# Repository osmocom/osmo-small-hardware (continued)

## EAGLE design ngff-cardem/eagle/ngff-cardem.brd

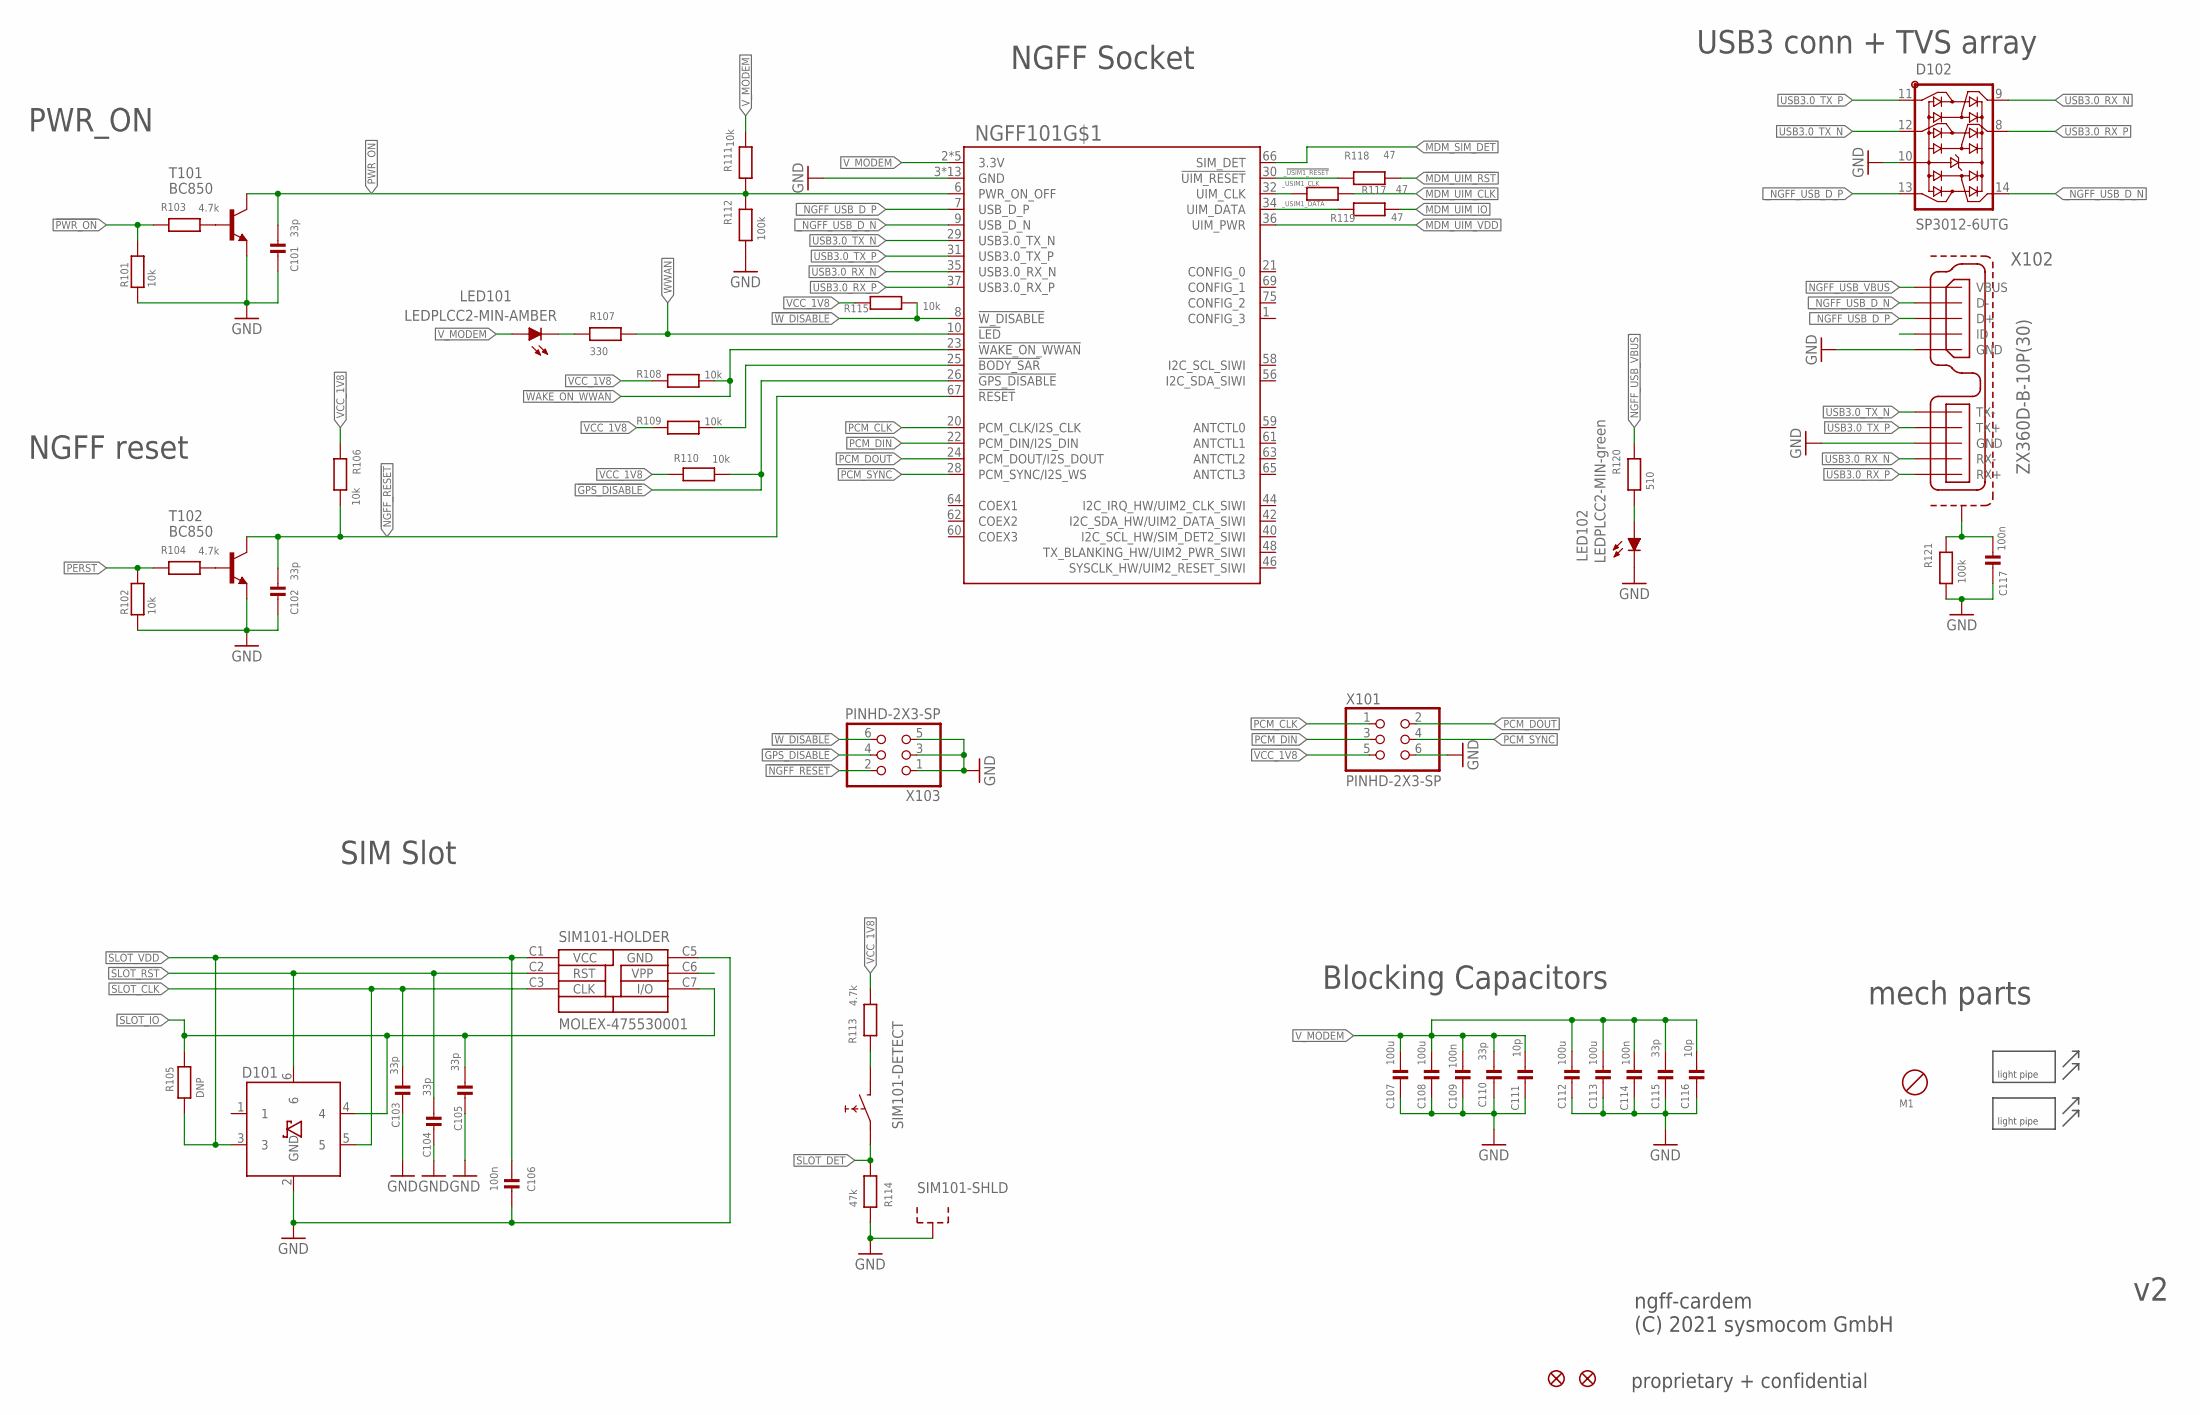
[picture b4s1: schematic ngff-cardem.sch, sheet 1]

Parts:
C101, C102, C103, C104, C105, C110, C115: 33p; _0402; MANUFACTURERPARTNUMBER CL05C330JB5NNNC
C106, C109, C114, C117: 100n; _0603; MANUFACTURERPARTNUMBER CC0603KRX7R7BB104
C107, C108, C112, C113: 100u; 1206; MANUFACTURERPARTNUMBER C3216X5R0J107M160AB
C111, C116: 10p; _0603; MANUFACTURERPARTNUMBER C0603C100F5GAC7867
D101: PESD5V0UBV; SOT666; MANUFACTURERPARTNUMBER PESD5V0U5BV,115
D102: SP3012-6UTG; UDFN-14; MANUFACTURERPARTNUMBER SP3012-06UTG
JP102, JP103: FIDUCIALUFIDUCIAL; MICRO-FIDUCIAL; MANUFACTURERPARTNUMBER UNKNOWN MANUFACTURER PART NUMBER
LED101: LEDPLCC2-MIN-AMBER; PLCC2-MIN; MANUFACTURERPARTNUMBER LO T676-S1T1-24-Z
LED102: LEDPLCC2-MIN-green; PLCC2-MIN; MANUFACTURERPARTNUMBER HSME-A100-M02J1
M2, M3: MENTOR_12701001; 1270.1001; MANUFACTURERPARTNUMBER UNKNOWN MANUFACTURER PART NUMBER
NGFF101: NGFF_B-NSOL; NGFF_3042_3052_NSOL; MANUFACTURERPARTNUMBER 2199230-3
R101, R102, R106, R108, R109, R110, R111, R115: 10k; _0603; MANUFACTURERPARTNUMBER CRG0603F10K/10
R103, R104, R113: 4.7k; _0603; MANUFACTURERPARTNUMBER RC0603JR-074K7L
R105: DNP; _0603; MANUFACTURERPARTNUMBER CRG0603F10K/10
R107: 330; _0603; MANUFACTURERPARTNUMBER RC0603FR-07330RL
R112, R121: 100k; _0603; MANUFACTURERPARTNUMBER RMCF0603FT100K
R114: 47k; _0603; MANUFACTURERPARTNUMBER RMCF0603FT47K0
R117, R118, R119: 47; _0402; MANUFACTURERPARTNUMBER CRGCQ0402F47R
R120: 510; _0603; MANUFACTURERPARTNUMBER RMCF0603FT510R
SIM101: MOLEX-475530001; MANUFACTURERPARTNUMBER 0475530001
T101, T102: BC850; SOT23-BEC; MANUFACTURERPARTNUMBER BC850C,235
X101, X103: PINHD-2X3-SP; 2X03; MANUFACTURERPARTNUMBER PR20203VBDN
X102: ZX360D-B-10P(30); ZX360D-B; MANUFACTURERPARTNUMBER ZX360D-B-10P(30)

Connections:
!BODY_SAR: NGFF101.25 (!BODY_SAR), R109.1
!GPS_DISABLE: NGFF101.26 (!GPS_DISABLE), R110.1, X103.4
!MDM_UIM_RST: R118.2; also elsewhere on the board
!NGFF_RESET: C102.1, NGFF101.67 (!RESET), R106.1, T102.C, X103.2
!PWR_ON: R101.1, R103.2; also elsewhere on the board
!SLOT_RST: C104.1, D101.6, SIM101.C2 (RST); also elsewhere on the board
!WAKE_ON_WWAN: NGFF101.23 (!WAKE_ON_WWAN), R108.1
!W_DISABLE: NGFF101.8 (!W_DISABLE), R115.1, X103.6
GND: C101.2, C102.2, C103.2, C104.2, C105.2, C106.2, C107.1, C108.1, C109.1, C110.2, C111.2, C112.1, C113.1, C114.1, C115.2, C116.2, C117.1, D101.2 (GND), D102.10 (GND), LED102.K (C), NGFF101.3 (GND), NGFF101.5 (GND), NGFF101.11 (GND), NGFF101.27 (GND), NGFF101.33 (GND), NGFF101.39 (GND), NGFF101.45 (GND), NGFF101.51 (GND), NGFF101.57 (GND), NGFF101.71 (GND), NGFF101.73 (GND), NGFF101.P$1 (GND), NGFF101.P$2 (GND), R101.2, R102.2, R112.1, R114.1, R121.1, SIM101.C5 (GND), SIM101.S1 (SHLD), SIM101.S2 (SHLD), T101.E, T102.E, X101.6, X102.5 (GND), X102.8 (GND), X103.1, X103.3, X103.5; also elsewhere on the board
MDM_SIM_DET: NGFF101.66 (SIM_DET); also elsewhere on the board
MDM_UIM_CLK: R117.2; also elsewhere on the board
MDM_UIM_IO: R119.2; also elsewhere on the board
MDM_UIM_VDD: NGFF101.36 (UIM_PWR); also elsewhere on the board
unnamed: R113.2, SIM101.CD2 (1)
unnamed: C117.2, R121.2, X102.S1, X102.S2 (S1), X102.S3 (S1), X102.S4 (S1), X102.S5 (S1), X102.S6 (S1), X102.S7 (S1), X102.S8 (S1)
unnamed: R104.1, T102.B
unnamed: R103.1, T101.B
unnamed: LED102.A, R120.1
unnamed: LED101.K (C), R107.1
NGFF_USB_VBUS: R120.2, X102.1 (VBUS)
PCM_CLK: NGFF101.20 (PCM_CLK/I2S_CLK), X101.1
PCM_DIN: NGFF101.22 (PCM_DIN/I2S_DIN), X101.3
PCM_DOUT: NGFF101.24 (PCM_DOUT/I2S_DOUT), X101.2
PCM_SYNC: NGFF101.28 (PCM_SYNC/I2S_WS), X101.4
PERST: R102.1, R104.2; also elsewhere on the board
PWR_ON: C101.1, NGFF101.6 (PWR_ON_OFF), R111.2, R112.2, T101.C
SLOT_CLK: C103.1, D101.5, SIM101.C3 (CLK); also elsewhere on the board
SLOT_DET: R114.2, SIM101.CD1 (0); also elsewhere on the board
SLOT_IO: C105.1, D101.4, R105.2, SIM101.C7 (I/O); also elsewhere on the board
SLOT_VDD: C106.1, D101.3, R105.1, SIM101.C1 (VCC); also elsewhere on the board
USB3.0_RX_N: D102.9 (7), NGFF101.35 (USB3.0_RX_N), X102.9 (RX-)
USB3.0_RX_P: D102.8 (6), NGFF101.37 (USB3.0_RX_P), X102.10 (RX+)
USB3.0_TX_N: D102.12 (2), NGFF101.29 (USB3.0_TX_N), X102.6 (TX-)
USB3.0_TX_P: D102.11 (1), NGFF101.31 (USB3.0_TX_P), X102.7 (TX+)
VCC_1V8: R106.2, R108.2, R109.2, R110.2, R113.1, R115.2, X101.5; also elsewhere on the board
V_MODEM: C107.2, C108.2, C109.2, C110.1, C111.1, C112.2, C113.2, C114.2, C115.1, C116.1, LED101.A, NGFF101.2 (3.3V), NGFF101.4 (3.3V), NGFF101.70 (3.3V), NGFF101.72 (3.3V), NGFF101.74 (3.3V), R111.1; also elsewhere on the board
WWAN: NGFF101.10 (!LED), R107.2; also elsewhere on the board
_!USIM1_RESET: NGFF101.30 (!UIM_RESET), R118.1
_NGFF_USB_D_N: D102.14 (5), NGFF101.9 (USB_D_N), X102.2 (D-)
_NGFF_USB_D_P: D102.13 (4), NGFF101.7 (USB_D_P), X102.3 (D+)
_USIM1_CLK: NGFF101.32 (UIM_CLK), R117.1
_USIM1_DATA: NGFF101.34 (UIM_DATA), R119.1

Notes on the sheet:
ngff-cardem (C) 2021 sysmocom GmbH
NGFF Socket
Blocking Capacitors
USB3 conn + TVS array
mech parts
SIM Slot
PWR_ON
NGFF reset

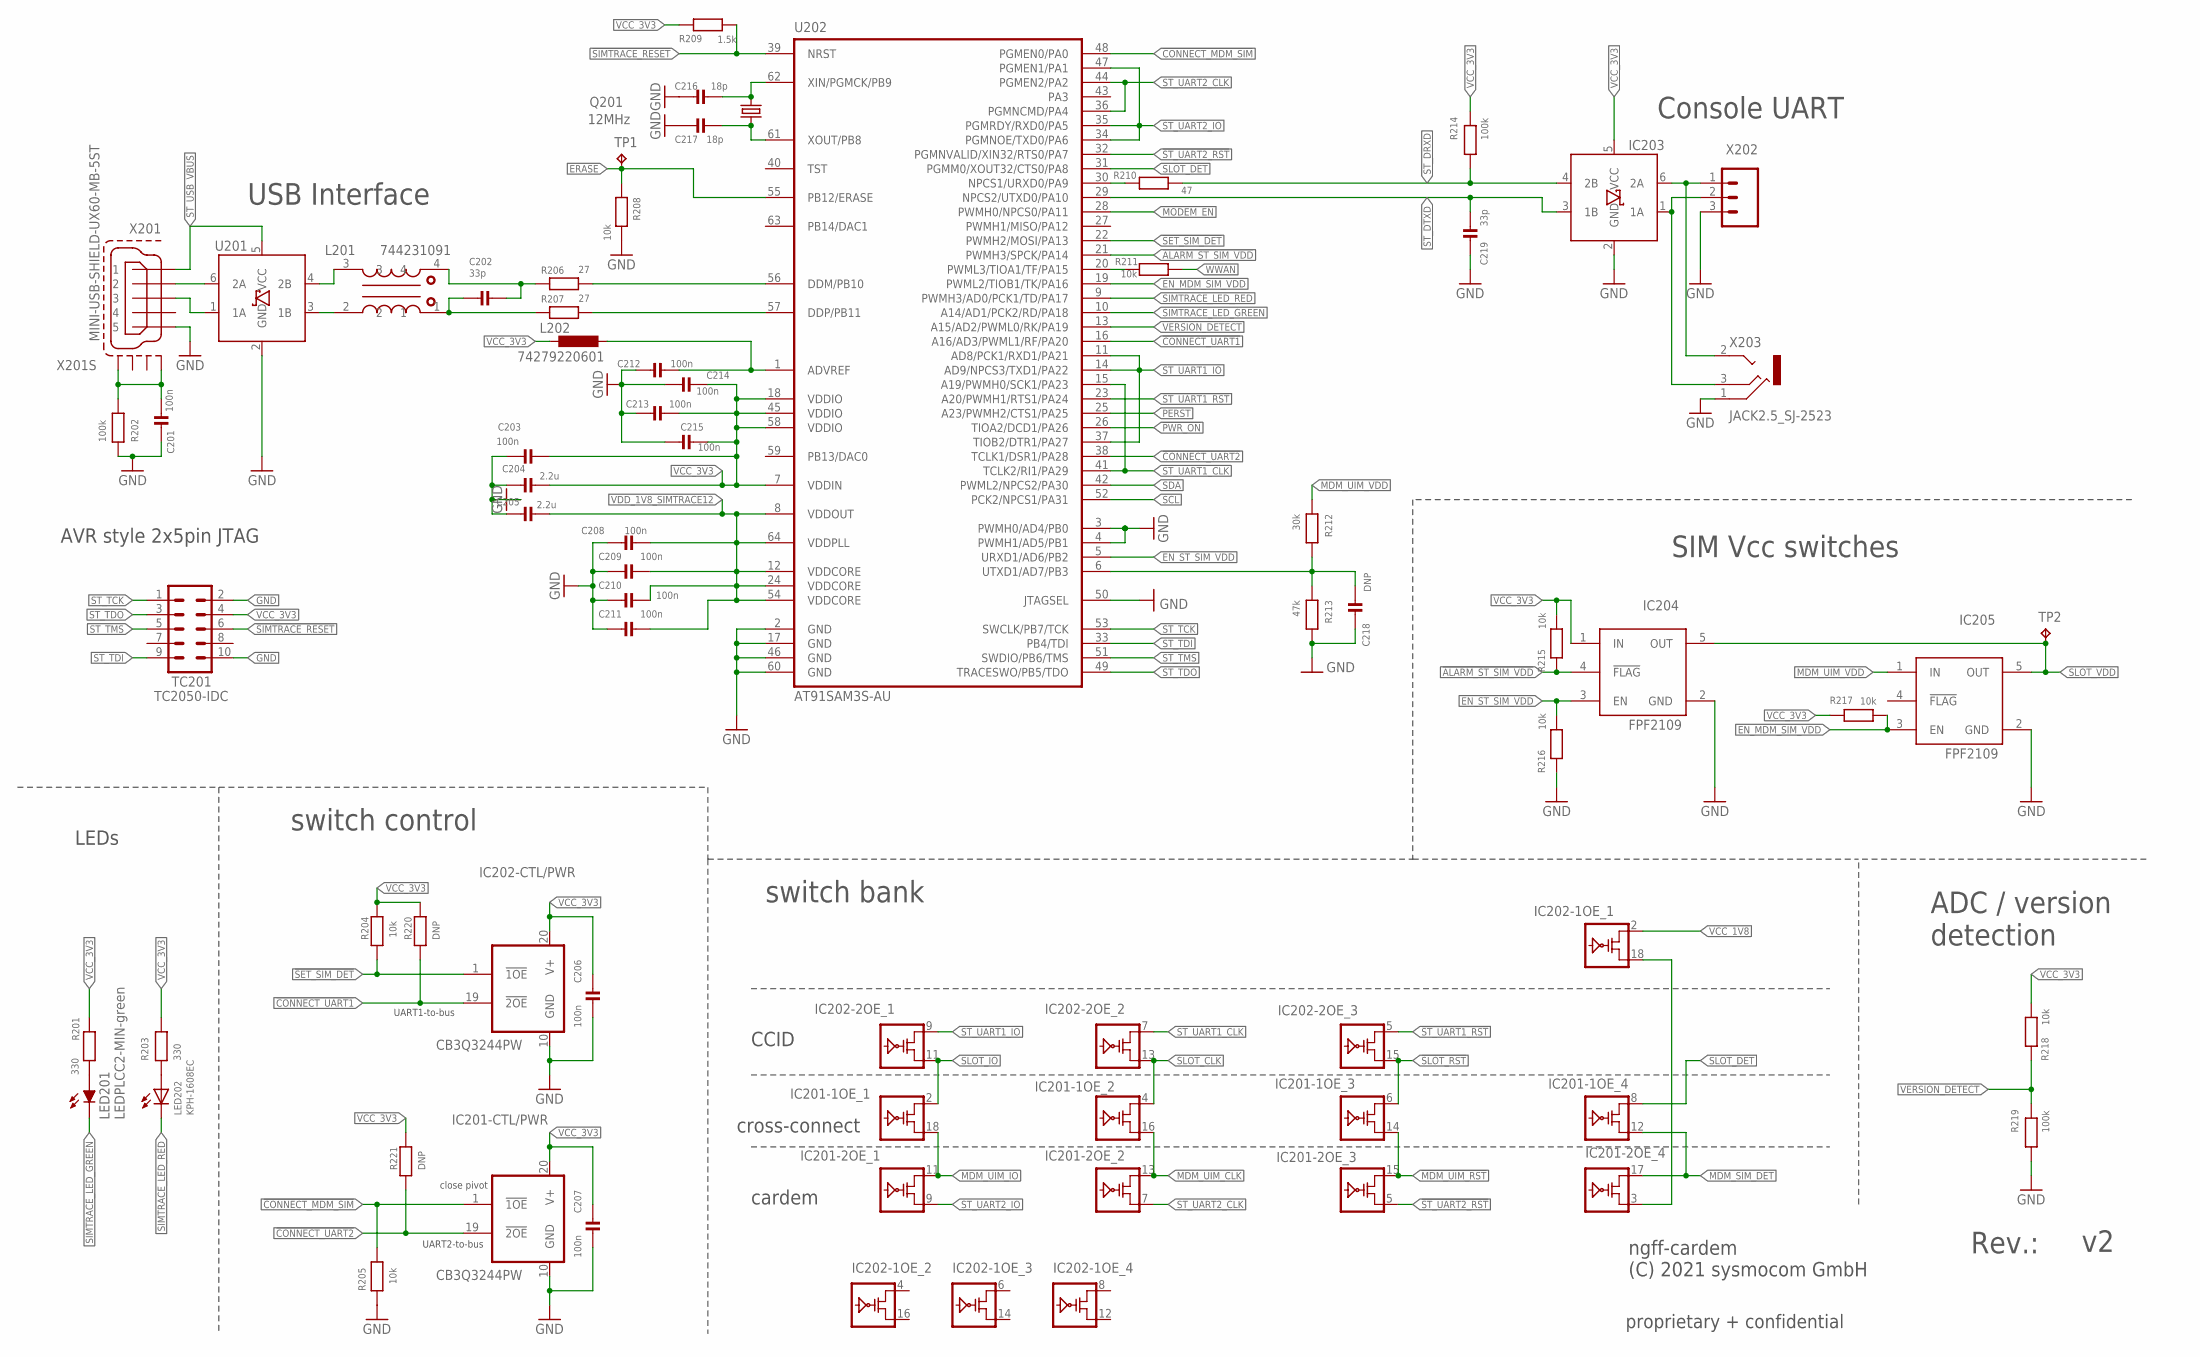
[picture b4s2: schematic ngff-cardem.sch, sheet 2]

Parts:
C201: 100n; _0603; MANUFACTURERPARTNUMBER CC0603KRX7R7BB104
C202, C219: 33p; _0402; MANUFACTURERPARTNUMBER CL05C330JB5NNNC
C203, C206, C207, C208, C209, C210, C211, C212, C213, C214, C215: 100n; _0402; MANUFACTURERPARTNUMBER CL05B104KO5NNWC
C204, C205: 2.2u; _0603; MANUFACTURERPARTNUMBER 0603ZD225KAT2A
C216, C217: 18p; _0603; MANUFACTURERPARTNUMBER GRM1885C2A180JA01D
C218: DNP; _0603; MANUFACTURERPARTNUMBER CC0402KRX7R7BB102
IC201, IC202: CB3Q3244PW; TSSOP20
IC203: IP4234CZ6; TSOP-6; MANUFACTURERPARTNUMBER IP4234CZ6,115
IC204, IC205: FPF2109; SOT23-5; MANUFACTURERPARTNUMBER FPF2109
L201: 744231091; WE-CNSW_0805; MANUFACTURERPARTNUMBER SRF2012A-900YA
L202: 74279220601; _0805; MANUFACTURERPARTNUMBER 74279220601
LED201: LEDPLCC2-MIN-green; PLCC2-MIN; MANUFACTURERPARTNUMBER HSME-A100-M02J1
LED202: KPH-1608EC; CHIP-LED0603; MANUFACTURERPARTNUMBER UNKNOWN MANUFACTURER PART NUMBER
Q201: 12MHz; HC49UP; MANUFACTURERPARTNUMBER CSM1Z-A5B2C3-40-12.0D18
R201, R203: 330; _0603; MANUFACTURERPARTNUMBER RC0603FR-07330RL
R202, R214, R219: 100k; _0603; MANUFACTURERPARTNUMBER RMCF0603FT100K
R204, R205, R208, R211, R215, R216, R217, R218: 10k; _0603; MANUFACTURERPARTNUMBER CRG0603F10K/10
R206, R207: 27; _0603; MANUFACTURERPARTNUMBER RC0603JR-0727RL
R209: 1.5k; _0603; MANUFACTURERPARTNUMBER CRGCQ0603F1K5
R210: 47; _0402; MANUFACTURERPARTNUMBER CRGCQ0402F47R
R212: 30k; _0603; MANUFACTURERPARTNUMBER RC0603FR-0730KL
R213: 47k; _0603; MANUFACTURERPARTNUMBER RMCF0603FT47K0
R220, R221: DNP; _0603; MANUFACTURERPARTNUMBER UNKNOWN MANUFACTURER PART NUMBER
TC201: TC2050-IDC; MANUFACTURERPARTNUMBER TC-2050
TP1, TP2: TPTP14R; TP14R; MANUFACTURERPARTNUMBER UNKNOWN MANUFACTURER PART NUMBER
U201: IP4234CZ6; TSOP-6; MANUFACTURERPARTNUMBER IP4234CZ6,115
U202: AT91SAM3S-AU; LQFP64; MANUFACTURERPARTNUMBER ATSAM3S4BA-AU
X201: MINI-USB-SHIELD-UX60-MB-5ST; UX60-MB-5ST
X202: 2.54mm; 1X03_LOCK; MANUFACTURERPARTNUMBER UNKNOWN MANUFACTURER PART NUMBER
X203: JACK2.5_SJ-2523; MANUFACTURERPARTNUMBER SJ-2523-SMT-TR

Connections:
!ALARM_ST_SIM_VDD: IC204.4 (!FLAG), R215.2, U202.21 (PWMH3/SPCK/PA14)
!CONNECT_MDM_SIM: IC201.1 (!1OE), R205.1, U202.48 (PGMEN0/PA0)
!CONNECT_UART1: IC202.19 (!2OE), R220.2, U202.16 (A16/AD3/PWML1/RF/PA20)
!CONNECT_UART2: IC201.19 (!2OE), R221.2, U202.38 (TCLK1/DSR1/PA28)
!MDM_UIM_RST: IC201.14 (B), IC201.15 (A); also elsewhere on the board
!PWR_ON: U202.26 (TIOA2/DCD1/PA26); also elsewhere on the board
!SET_SIM_DET: IC202.1 (!1OE), R204.2, U202.22 (PWMH2/MOSI/PA13)
!SIMTRACE_RESET: R209.1, TC201.6, U202.39 (NRST)
!SLOT_RST: IC201.6 (A), IC202.15 (A); also elsewhere on the board
!ST_UART1_RST: IC202.5 (B), U202.23 (A20/PWMH1/RTS1/PA24)
!ST_UART2_RST: IC201.5 (B), U202.32 (PGMNVALID/XIN32/RTS0/PA7)
EN_MDM_SIM_VDD: IC205.3 (EN), R217.1, U202.19 (PWML2/TIOB1/TK/PA16)
EN_ST_SIM_VDD: IC204.3 (EN), R216.1, U202.5 (URXD1/AD6/PB2)
ERASE: R208.2, TP1.TP, U202.55 (PB12/ERASE)
GND: C201.1, C203.1, C204.1, C205.1, C206.1, C207.1, C208.1, C209.1, C210.1, C211.1, C212.1, C213.1, C214.1, C215.1, C216.2, C217.2, C218.2, C219.2, IC201.10 (GND), IC202.10 (GND), IC203.2 (GND), IC204.2 (GND), IC205.2 (GND), R202.2, R205.2, R208.1, R213.1, R216.2, R219.1, TC201.2, TC201.10, U201.2 (GND), U202.2 (GND), U202.3 (PWMH0/AD4/PB0), U202.4 (PWMH1/AD5/PB1), U202.17 (GND), U202.46 (GND), U202.50 (JTAGSEL), U202.60 (GND), X201.5, X202.3, X203.1 (RING); also elsewhere on the board
MDM_SIM_DET: IC201.12 (B), IC201.17 (A); also elsewhere on the board
MDM_UIM_CLK: IC201.13 (A), IC201.16 (B); also elsewhere on the board
MDM_UIM_IO: IC201.11 (A), IC201.18 (B); also elsewhere on the board
MDM_UIM_VDD: IC205.1 (IN), R212.2; also elsewhere on the board
MODEM_EN: U202.28 (PWMH0/NPCS0/PA11); also elsewhere on the board
unnamed: L201.2, U201.3 (1B)
unnamed: L201.3, U201.4 (2B)
unnamed: LED202.A, R203.2
unnamed: IC201.3 (B), IC202.18 (B)
unnamed: R210.1, U202.30 (NPCS1/URXD0/PA9)
unnamed: C201.2, R202.1, X201.M1 (S1), X201.M4 (S4)
unnamed: LED201.A, R201.1
unnamed: C216.1, Q201.2, U202.62 (XIN/PGMCK/PB9)
unnamed: C217.1, Q201.1, U202.61 (XOUT/PB8)
unnamed: C218.1, R212.1, R213.2, U202.6 (UTXD1/AD7/PB3)
unnamed: R211.2, U202.20 (PWML3/TIOA1/TF/PA15)
unnamed: IC203.6 (2A), X202.1, X203.2 (TIP)
unnamed: C212.2, L202.2, U202.1 (ADVREF)
PERST: U202.25 (A23/PWMH2/CTS1/PA25); also elsewhere on the board
SCL: U202.52 (PCK2/NPCS1/PA31)
SDA: U202.42 (PWML2/NPCS2/PA30)
SIMTRACE12_USB_D_N: C202.1, L201.4, R206.1
SIMTRACE12_USB_D_P: C202.2, L201.1, R207.1
SIMTRACE_LED_GREEN: LED201.K (C), U202.10 (A14/AD1/PCK2/RD/PA18)
SIMTRACE_LED_RED: LED202.C, U202.9 (PWMH3/AD0/PCK1/TD/PA17)
SLOT_CLK: IC201.4 (A), IC202.13 (A); also elsewhere on the board
SLOT_DET: IC201.8 (A), U202.31 (PGMM0/XOUT32/CTS0/PA8); also elsewhere on the board
SLOT_IO: IC201.2 (A), IC202.11 (A); also elsewhere on the board
SLOT_VDD: IC204.5 (OUT), IC205.5 (OUT), TP2.TP; also elsewhere on the board
ST_DRXD: IC203.4 (2B), R210.2, R214.1
ST_DTXD: C219.1, IC203.3 (1B), U202.29 (NPCS2/UTXD0/PA10)
ST_TCK: TC201.1, U202.53 (SWCLK/PB7/TCK)
ST_TDI: TC201.9, U202.33 (PB4/TDI)
ST_TDO: TC201.3, U202.49 (TRACESWO/PB5/TDO)
ST_TMS: TC201.5, U202.51 (SWDIO/PB6/TMS)
ST_UART1_CLK: IC202.7 (B), U202.15 (A19/PWMH0/SCK1/PA23), U202.41 (TCLK2/RI1/PA29)
ST_UART1_IO: IC202.9 (B), U202.11 (AD8/PCK1/RXD1/PA21), U202.14 (AD9/NPCS3/TXD1/PA22), U202.37 (TIOB2/DTR1/PA27)
ST_UART2_CLK: IC201.7 (B), U202.36 (PGMNCMD/PA4), U202.44 (PGMEN2/PA2)
ST_UART2_IO: IC201.9 (B), U202.34 (PGMNOE/TXD0/PA6), U202.35 (PGMRDY/RXD0/PA5), U202.47 (PGMEN1/PA1)
ST_USB_VBUS: U201.5 (VCC), X201.1
UART_TX0: IC203.1 (1A), X202.2, X203.3 (MIDDLE)
VCC_1V8: IC202.2 (A); also elsewhere on the board
VCC_3V3: C203.2, C204.2, C206.2, C207.2, C213.2, C214.2, C215.2, IC201.20 (V+), IC202.20 (V+), IC203.5 (VCC), IC204.1 (IN), L202.1, R201.2, R203.1, R204.1, R209.2, R214.2, R215.1, R217.2, R218.1, R220.1, R221.1, TC201.4, U202.7 (VDDIN), U202.18 (VDDIO), U202.45 (VDDIO), U202.58 (VDDIO); also elsewhere on the board
VDD_1V8_SIMTRACE12: C205.2, C208.2, C209.2, C210.2, C211.2, U202.8 (VDDOUT), U202.12 (VDDCORE), U202.24 (VDDCORE), U202.54 (VDDCORE), U202.64 (VDDPLL)
VERSION_DETECT: R218.2, R219.2, U202.13 (A15/AD2/PWML0/RK/PA19)
WWAN: R211.1; also elsewhere on the board
_SIMTRACE12_USB_D_N: R206.2, U202.56 (DDM/PB10)
_SIMTRACE12_USB_D_P: R207.2, U202.57 (DDP/PB11)
_USB_D_N1: U201.6 (2A), X201.2
_USB_D_P1: U201.1 (1A), X201.3

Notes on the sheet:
AVR style 2x5pin JTAG
Rev.:
switch control
LEDs
Console UART
ADC / version detection
ngff-cardem (C) 2021 sysmocom GmbH
USB Interface
switch bank
UART1-to-bus
UART2-to-bus
close pivot
SIM Vcc switches
cardem
CCID
cross-connect

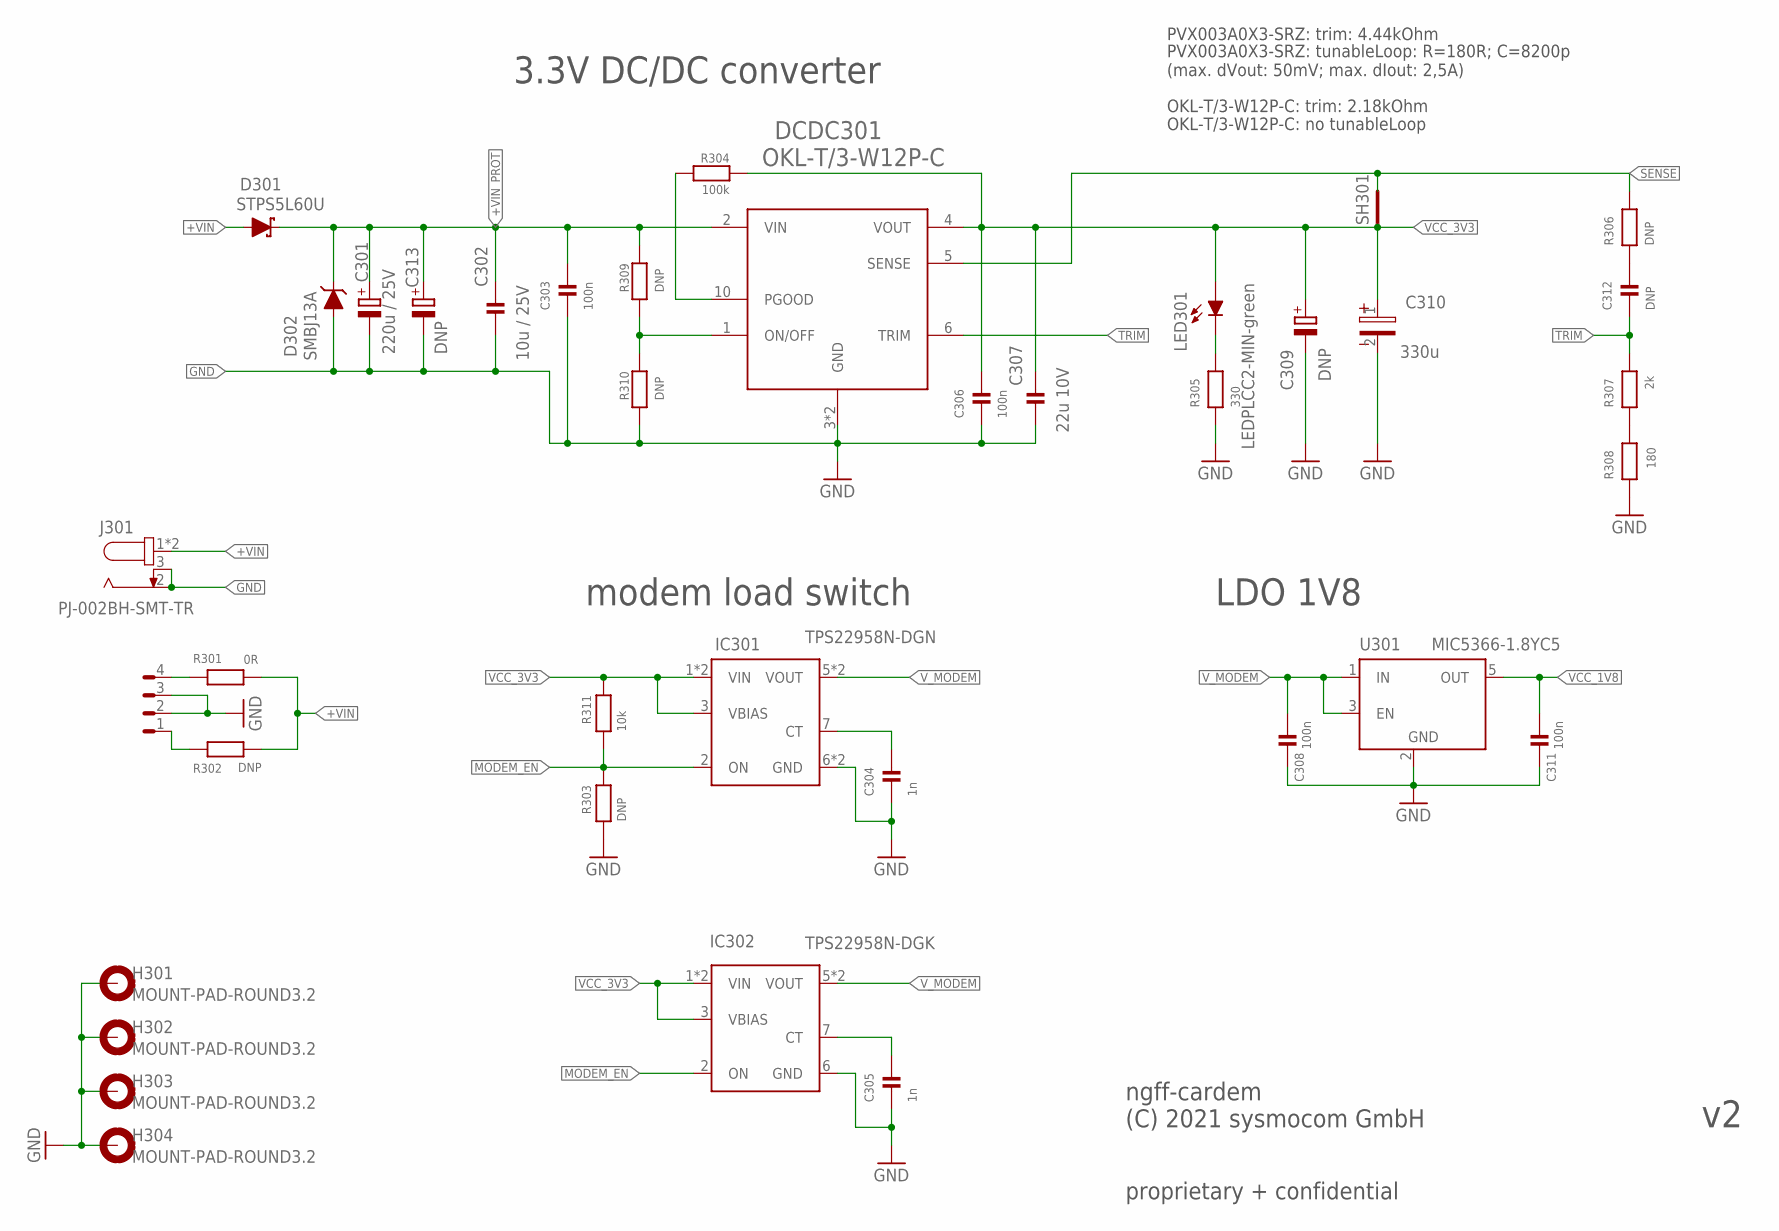
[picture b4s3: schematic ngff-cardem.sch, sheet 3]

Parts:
C301: 220u / 25V; UD-8X10_NICHICON; MANUFACTURERPARTNUMBER UUD1E221MNL1GS
C302: 10u / 25V; C1812K; MANUFACTURERPARTNUMBER C4532X7R1E106M250KA
C303, C306, C308, C311: 100n; _0603; MANUFACTURERPARTNUMBER CC0603KRX7R7BB104
C304, C305: 1n; _0603; MANUFACTURERPARTNUMBER CL10B102KB8NNNC
C307: 22u 10V; 1206; MANUFACTURERPARTNUMBER CL31A476MPHNNNE
C309: DNP; SMC_B; MANUFACTURERPARTNUMBER F920J107MBA
C310: 330u; 4.2X1.9X2.8(BXCXA); MANUFACTURERPARTNUMBER APXF6R3ARA331MH70G
C312: DNP; _0603; MANUFACTURERPARTNUMBER UNKNOWN MANUFACTURER PART NUMBER
C313: DNP; UD-8X10_NICHICON; MANUFACTURERPARTNUMBER UNKNOWN MANUFACTURER PART NUMBER
D301: STPS5L60U; SMBDIODE; MANUFACTURERPARTNUMBER B350B-13-F
D302: SMBJ13A; SMBDIODE; MANUFACTURERPARTNUMBER SZP6SMB16AT3G
DCDC301: OKL-T/3-W12P-C; DC-DC_CON-ALLPADS; MANUFACTURERPARTNUMBER OKL-T/3-W12P-C
H301, H302, H303, H304: MOUNT-PAD-ROUND3.2; 3,2-PAD; MANUFACTURERPARTNUMBER UNKNOWN MANUFACTURER PART NUMBER
IC301: TPS22958N-DGN; HVSSOP8; MANUFACTURERPARTNUMBER TPS22958DGNR
IC302: TPS22958N-DGK; VSSOP8; MANUFACTURERPARTNUMBER TPS22958NDGKR
J301: PJ-002BH-SMT-TR; 694108106102; MANUFACTURERPARTNUMBER PJ-002BH-SMT-TR
LED301: LEDPLCC2-MIN-green; PLCC2-MIN; MANUFACTURERPARTNUMBER HSME-A100-M02J1
R301: 0R; 1210; MANUFACTURERPARTNUMBER TLRZ2BTTD
R302: DNP; 1210; MANUFACTURERPARTNUMBER TLRZ2BTTD
R303, R306, R309, R310: DNP; _0603; MANUFACTURERPARTNUMBER UNKNOWN MANUFACTURER PART NUMBER
R304: 100k; _0603; MANUFACTURERPARTNUMBER RMCF0603FT100K
R305: 330; _0603; MANUFACTURERPARTNUMBER RC0603FR-07330RL
R307: 2k; _0603; MANUFACTURERPARTNUMBER RC0603FR-072KL
R308: 180; _0603; MANUFACTURERPARTNUMBER CRGCQ0603F180R
R311: 10k; _0603; MANUFACTURERPARTNUMBER CRG0603F10K/10
SH301: SHORT-HT5; SHORT_TOP-50; MANUFACTURERPARTNUMBER UNKNOWN MANUFACTURER PART NUMBER
U301: MIC5366-1.8YC5; SC70-5; MANUFACTURERPARTNUMBER MIC5366-1.8YC5-TR
X301: 171826-4-RA; 171826-4; MANUFACTURERPARTNUMBER 171826-4

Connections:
+VIN: D301.A, J301.1, J301.1-1 (1), R301.2, R302.1
+VIN_PROT: C301.+, C302.1, C303.2, C313.+, D301.C, D302.C, DCDC301.2 (VIN), R309.1
GND: C301.-, C302.2, C303.1, C304.1, C305.1, C306.1, C307.2, C308.1, C309.-, C310.2, C311.1, C313.-, D302.A, DCDC301.3 (GND), DCDC301.7 (GND), H301.B3,2, H302.B3,2, H303.B3,2, H304.B3,2, IC301.6 (GND), IC301.EXP (GND), IC302.6 (GND), J301.2, J301.3, R303.1, R305.1, R308.2, R310.2, U301.2 (GND), X301.2, X301.3; also elsewhere on the board
MODEM_EN: IC301.2 (ON), IC302.2 (ON), R303.2, R311.1; also elsewhere on the board
unnamed: C312.2, R306.2
unnamed: LED301.K (C), R305.2
unnamed: DCDC301.10 (PGOOD), R304.2
unnamed: C305.2, IC302.7 (CT)
unnamed: R301.1, X301.4
unnamed: R302.2, X301.1
unnamed: DCDC301.1 (ON/OFF), R309.2, R310.1
unnamed: R307.2, R308.1
unnamed: C304.2, IC301.7 (CT)
SENSE: DCDC301.5 (SENSE), R306.1, SH301.2
TRIM: C312.1, DCDC301.6 (TRIM), R307.1
VCC_1V8: C311.2, U301.5 (OUT); also elsewhere on the board
VCC_3V3: C306.2, C307.1, C309.+, C310.1, DCDC301.4 (VOUT), IC301.1 (VIN), IC301.3 (VBIAS), IC301.4 (VIN), IC302.1 (VIN), IC302.3 (VBIAS), IC302.4 (VIN), LED301.A, R304.1, R311.2, SH301.1; also elsewhere on the board
V_MODEM: C308.2, IC301.5 (VOUT), IC301.8 (VOUT), IC302.5 (VOUT), IC302.8 (VOUT), U301.1 (IN), U301.3 (EN); also elsewhere on the board

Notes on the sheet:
3.3V DC/DC converter
ngff-cardem (C) 2021 sysmocom GmbH
PVX003A0X3-SRZ: tunableLoop: R=180R; C=8200p (max. dVout: 50mV; max. dIout: 2,5A)
PVX003A0X3-SRZ: trim: 4.44kOhm
modem load switch
LDO 1V8
OKL-T/3-W12P-C: no tunableLoop
OKL-T/3-W12P-C: trim: 2.18kOhm

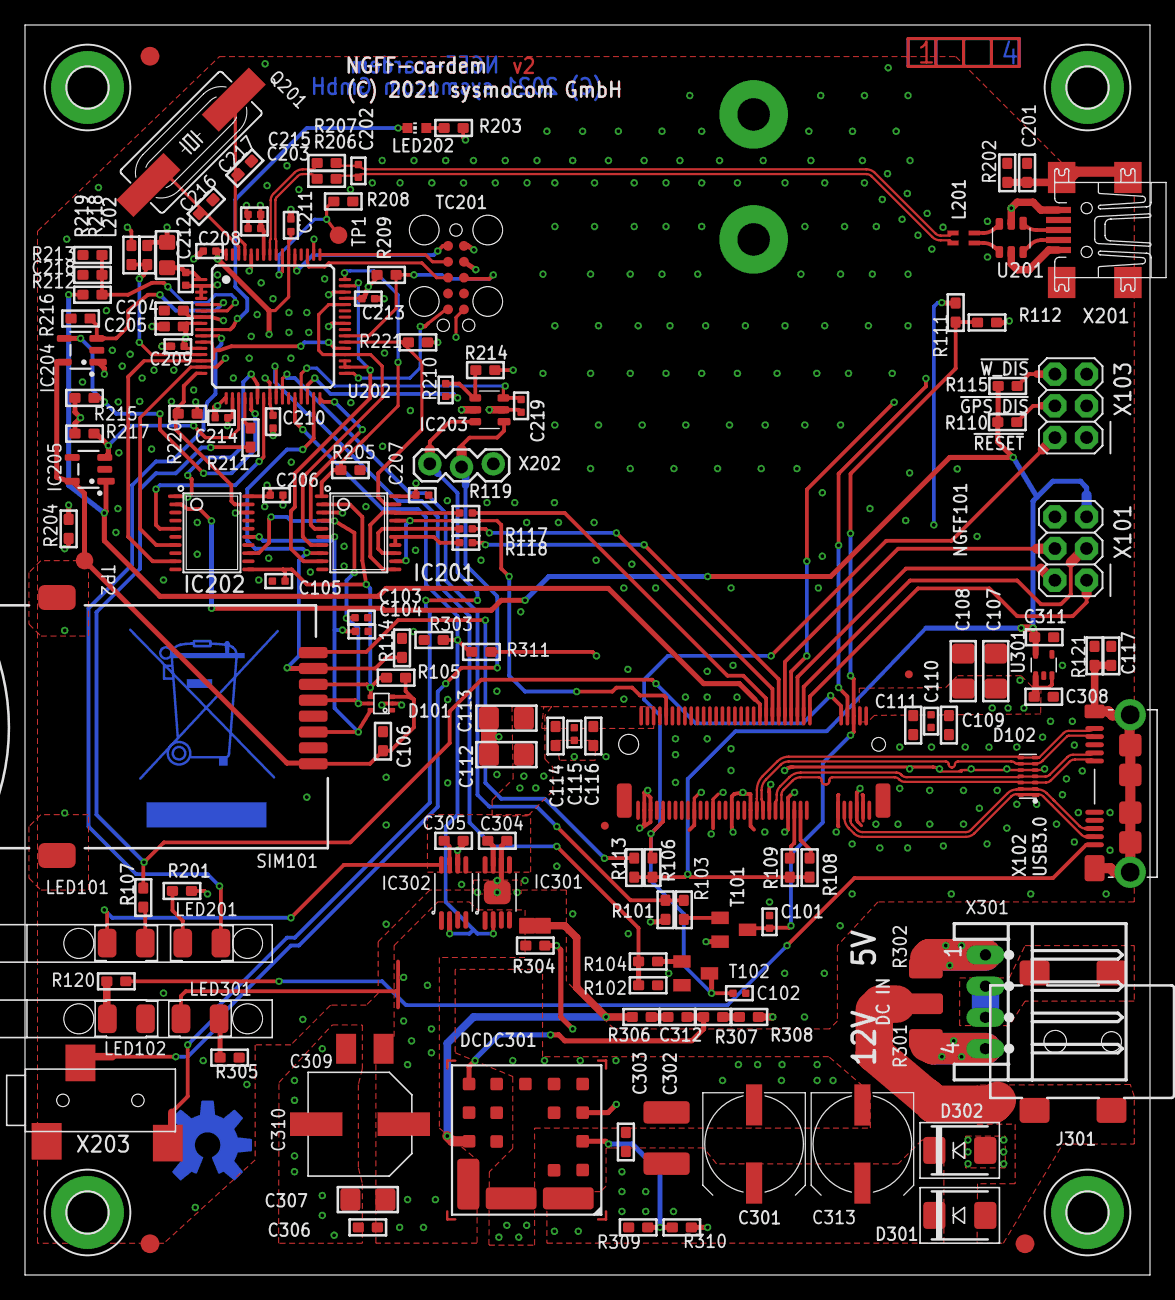
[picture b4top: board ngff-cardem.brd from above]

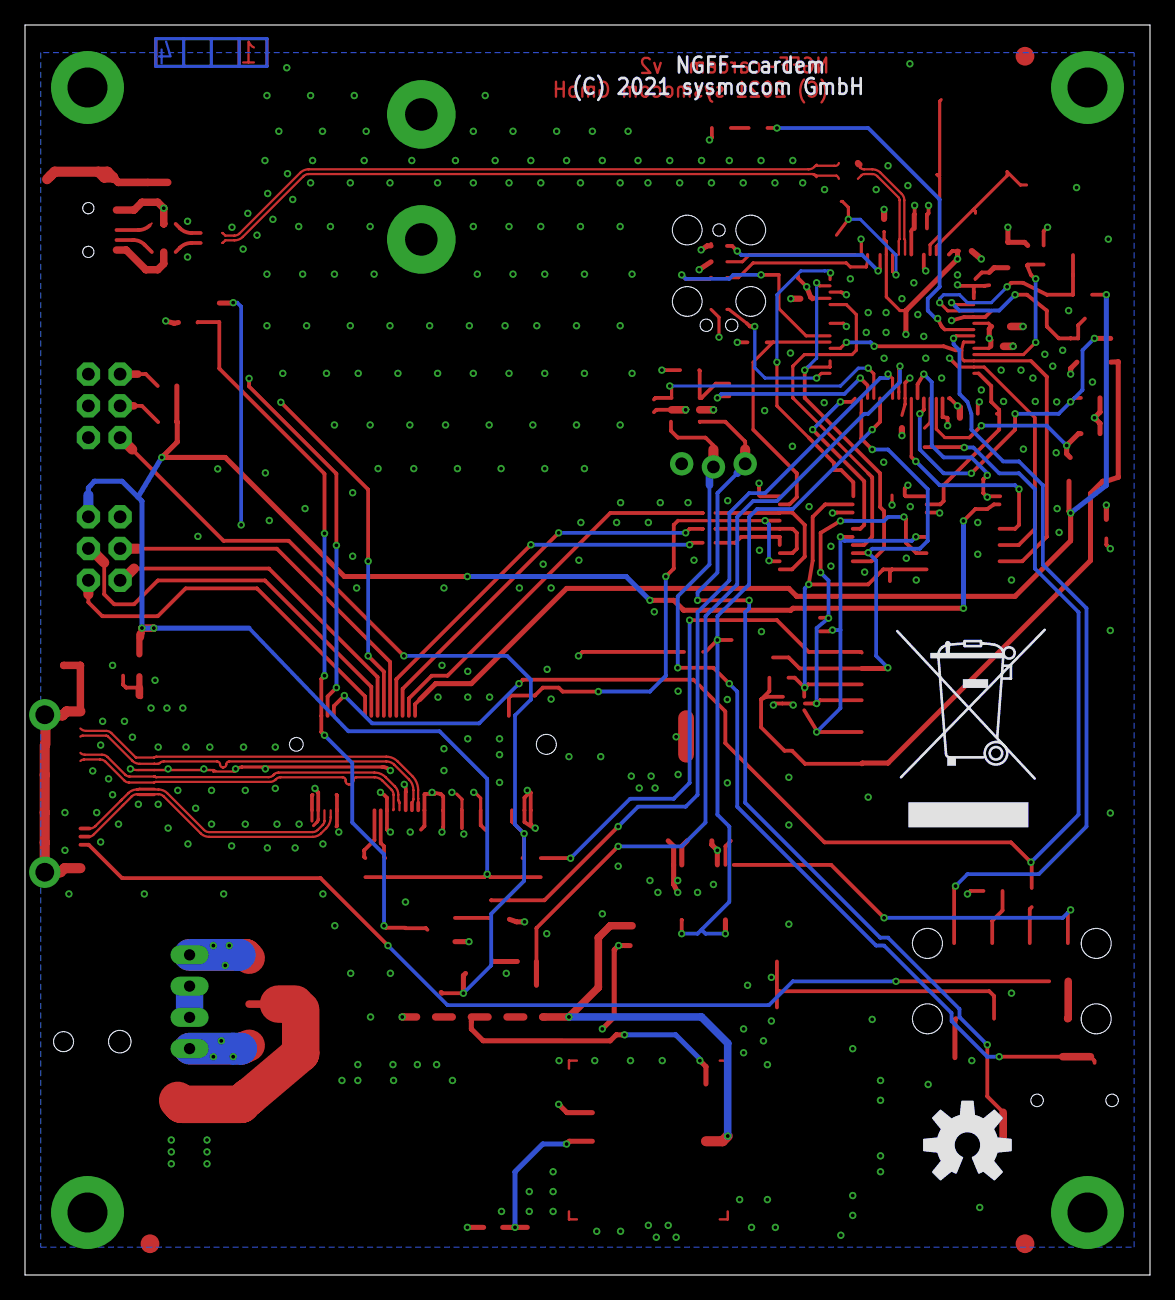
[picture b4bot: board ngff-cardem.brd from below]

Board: 4 copper layers, 90.0 x 100.0 mm, 155 parts (4 on the bottom side), 103 nets.

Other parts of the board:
FID1, FID2, FID3: VISION_REF15
LOGO1: OSHW-LOGOL-COPPER; OSHW-LOGO-L_COPPER
U$1: WEEE_BIN_TOP
U$2: WEEE_BIN
U$7: OSHW-LOGO-L

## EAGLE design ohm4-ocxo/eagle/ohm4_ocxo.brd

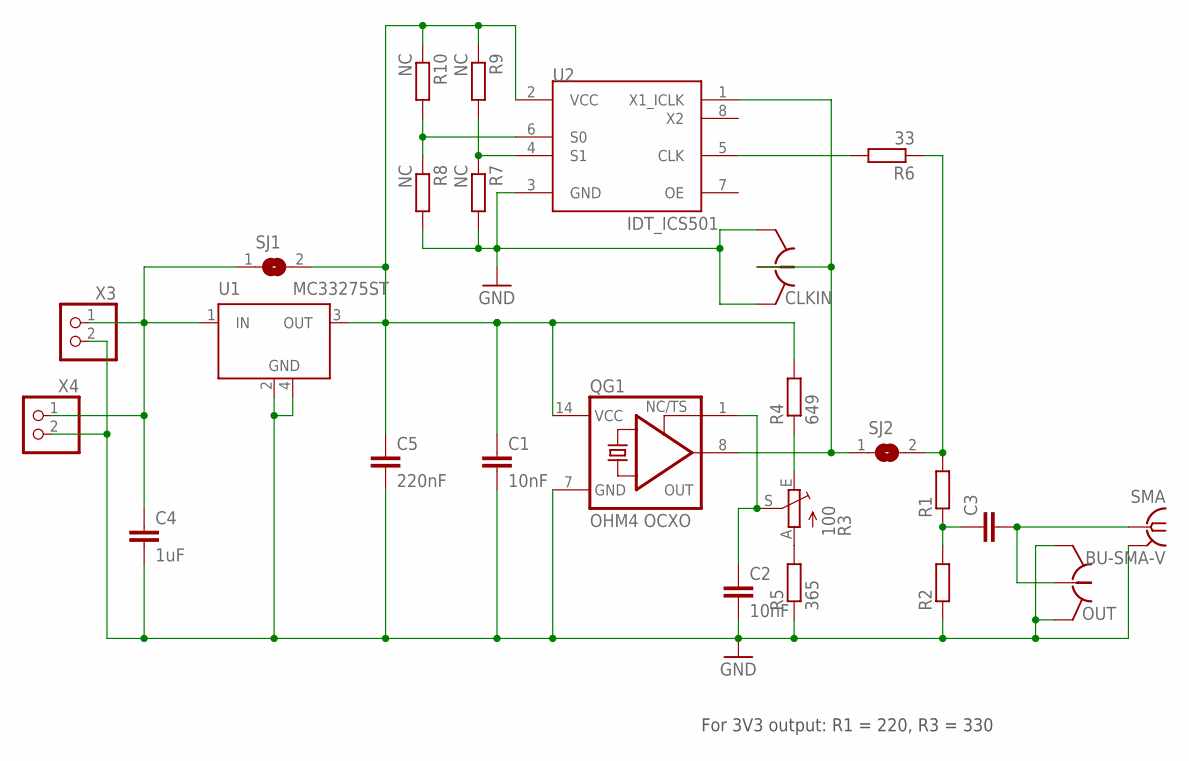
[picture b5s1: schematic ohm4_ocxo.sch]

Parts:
C1, C2: 10nF; C0603
C3: C-EUC0603; C0603
C4: 1uF; C0603
C5: 220nF; C0603
CLKIN: HRS_UFL
OUT: HRS_UFL
QG1: OHM4 OCXO; DIL14S
R1, R2: R-EU_R0603; R0603
R3: 100; PT-SPIN
R4: 649; R0603
R5: 365; R0603
R6: 33; R0603
R7, R8, R9, R10: NC; R0603
SJ1, SJ2: SJ
SMA: BU-SMA-V
U1: MC33275ST; SOT223
U2: IDT_ICS501; SOIC08
X3, X4: PINHD-1X2; 1X02

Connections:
GND: C1.2, C2.2, C4.2, C5.2, CLKIN.GND@1 (GND), CLKIN.GND@2 (GND), OUT.GND@1 (GND), OUT.GND@2 (GND), QG1.7 (GND), R2.1, R5.1, R7.2, R8.2, SMA.2 (GND), SMA.3 (GND), SMA.4 (GND), SMA.5 (GND), U1.2 (GND), U1.4 (GND1), U2.3 (GND), X3.2, X4.2
unnamed: C3.1, R1.1, R2.2
unnamed: C4.1, SJ1.1, U1.1 (IN), X3.1, X4.1
unnamed: R1.2, R6.1, SJ2.2
unnamed: C2.1, QG1.1 (TS), R3.S
unnamed: CLKIN.SIG (1), QG1.8 (OUT), SJ2.1, U2.1 (X1_ICLK)
unnamed: R6.2, U2.5 (CLK)
unnamed: R7.1, R9.2, U2.4 (S1)
unnamed: R8.1, R10.2, U2.6 (S0)
unnamed: R3.A, R5.2
unnamed: R3.E, R4.1
unnamed: C3.2, OUT.SIG (1), SMA.1
VCC: C1.1, C5.1, QG1.14 (VCC), R4.2, R9.1, R10.1, SJ1.2, U1.3 (OUT), U2.2 (VCC)

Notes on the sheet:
For 3V3 output: R1 = 220, R3 = 330

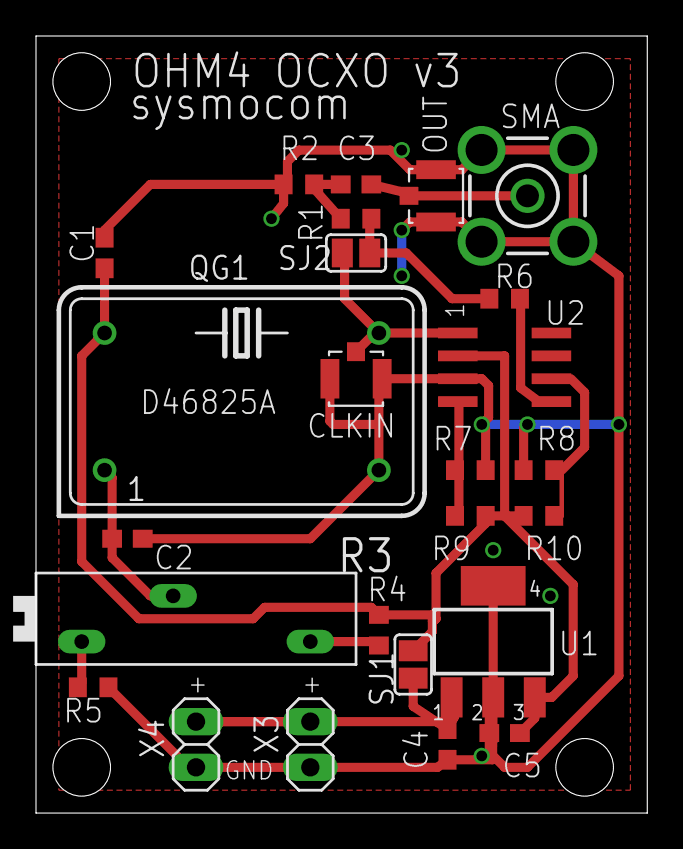
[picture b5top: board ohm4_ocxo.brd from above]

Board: 2 copper layers, 34.0 x 43.2 mm, 25 parts (0 on the bottom side), 13 nets.
